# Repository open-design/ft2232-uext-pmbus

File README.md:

UEXT/TI PMBus Adapter board for popular FT2232H-based modules.

## Schematic

## BOM

| name | designation | designator | quantity | supply | datasheets |
| ---  | ---         | ---        | ---      | ---    | ---        |
| CONNFLY PBD-26 | Conn_02x13_Odd_Even | J1,J2 | 2 |  [electronshik.ru](https://www.electronshik.ru/item/CONNFLY/PBD-26)<br /> | [pdf](https://static.chipdip.ru/lib/226/DOC000226931.pdf) |
| CONNFLY PBS-22 | Conn_01x22_Female | J3,J4 | 2 |  [electronshik.ru](https://www.electronshik.ru/item/CONNFLY/PBS-22%20DS1023-1x22S21)<br /> | [pdf](https://static.chipdip.ru/lib/226/DOC000226931.pdf) |
| CONNFLY BH-10 | Conn_02x05_Odd_Even | J5,J6 | 2 |  [electronshik.ru](https://www.electronshik.ru/item/CONNFLY/BH-10)<br /> | [pdf](https://static.chipdip.ru/lib/463/DOC002463525.pdf) |
| CONNFLY PLS-2 | Jumper | JP1,JP2 | 2 |  [electronshik.ru](https://www.electronshik.ru/item/CONNFLY/PLS-2)<br /> | [pdf](https://static.chipdip.ru/lib/227/DOC000227157.pdf) |
| CONNFLY DS1027-2 ABF10 |  |  | 2 |  [electronshik.ru](https://www.electronshik.ru/item/CONNFLY/DS1027-2%20ABF10) | [pdf](https://static.chipdip.ru/lib/884/DOC003884776.pdf) |
| YAGEO RC0805FR-0710KL | 10K/1% | R1,R2 | 2 |  [electronshik.ru](https://www.electronshik.ru/item/YAG/RC0805FR-0710KL)<br /> [digikey.com](https://www.digikey.com/products/en?keywords=RC0805FR-0710KL)<br /> [mouser.com](https://mouser.com/Search/Refine.aspx?Keyword=RC0805FR-0710KL)<br /> [farnell.com](https://uk.farnell.com/search?st=RC0805FR-0710KL)<br /> | [pdf](http://www.yageo.com/exep/pages/download/literatures/ProductSelectionGuide_2018_Final.pdf#page=8) |

## Links

* [Dangerous Prototypes FT2232 breakout board](http://dangerousprototypes.com/docs/FT2232_breakout_board)
* http://microsin.net/adminstuff/hardware/ft2232h-board.html
* [FT2232H Mini ModuleUSB Hi-Speed FT2232H Evaluation Module](https://www.ftdichip.com/Support/Documents/DataSheets/Modules/DS_FT2232H_Mini_Module.pdf)
* [FT2232H-56Q Mini ModuleUSB Hi-Speed FT2232H Evaluation Module](https://www.ftdichip.com/Support/Documents/DataSheets/Modules/DS_FT2232H-56Q_Mini_Module.pdf)
* [FT2232SPI Programmer](https://www.flashrom.org/FT2232SPI_Programmer)
* [Olimex UEXT board to board connector](https://www.olimex.com/Products/Modules/UEXT/)
* [Texas Instruments USB Interface Adapter Evaluation Module (USB-TO-GPIO), SLLU093](http://www.ti.com/lit/ml/sllu093/sllu093.pdf)

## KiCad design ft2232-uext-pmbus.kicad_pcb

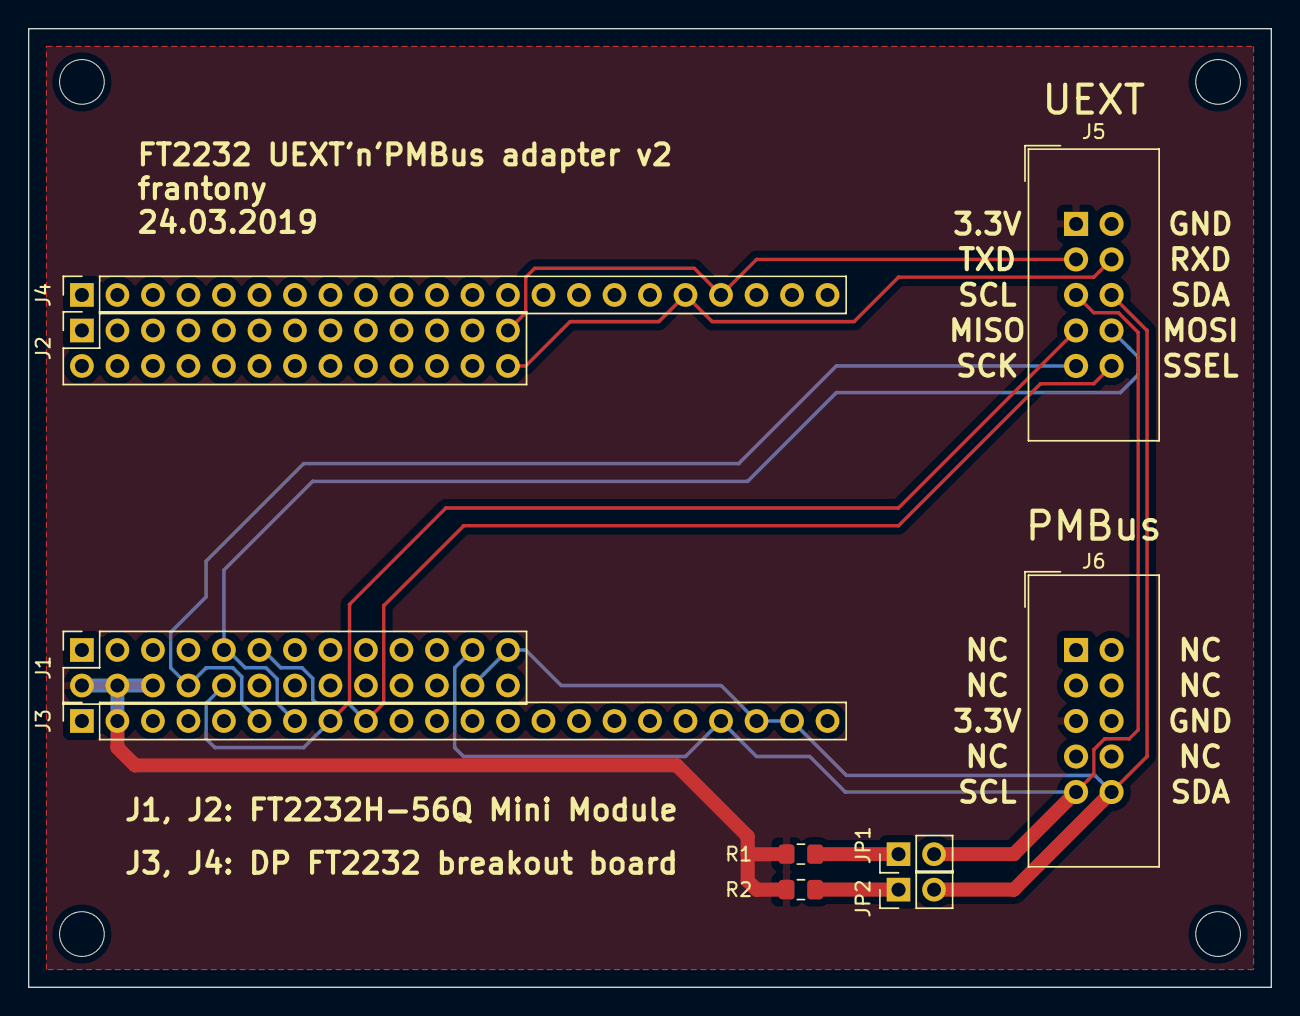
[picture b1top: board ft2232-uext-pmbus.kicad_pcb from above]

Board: 2 copper layers, 88.9 x 68.6 mm, 14 parts (0 on the bottom side), 12 nets.

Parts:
J1, J2: Conn_02x13_Odd_Even; PinSocket_2x13_P2.54mm_Vertical
J3, J4: Conn_01x22_Female; PinSocket_1x22_P2.54mm_Vertical
J5, J6: Conn_02x05_Odd_Even; IDC-Header_2x05_P2.54mm_Vertical
JP1, JP2: Jumper; PinHeader_1x02_P2.54mm_Vertical
MK1, MK2, MK3, MK4: MountingHole; MountingHole_3.2mm_M3
R1, R2: 10K/1%; R_0805_2012Metric_Pad1.15x1.40mm_HandSolder

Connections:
/GND: J1.1, J1.3, J1.5, J2.1, J2.3, J3.4, J4.2, J5.2, J6.6
/MISO: J1.10, J3.8, J5.7
/MOSI: J1.9, J3.7, J5.8
/RXD: J2.26, J4.18, J5.4
/SCK: J1.8, J3.6, J5.9
/SCL: J1.23, J3.19, J5.5, J6.9, JP1.2
/SDA: J1.24, J1.25, J3.20, J3.21, J5.6, J6.10, JP2.2
/SSEL: J1.11, J3.9, J5.10
/TXD: J2.25, J4.19, J5.3
/VCC3V3: J1.2, J1.4, J1.6, J3.2, J5.1, J6.5, R1.1, R2.1
unnamed: JP1.1, R1.2
unnamed: JP2.1, R2.2

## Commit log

2019-06-22 FT2232 UEXT'n'PMBus adapter v2
2019-06-23 add docs
